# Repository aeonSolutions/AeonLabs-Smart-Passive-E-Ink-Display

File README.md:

[PCB-Prototyping-Catalogue](https://github.com/aeonSolutions/PCB-Prototyping-Catalogue)  >>  [Smart LCD Touch Displays](https://github.com/aeonSolutions/PCB-Prototyping-Catalogue/tree/main/Smart%20LCD%20Touch%20Displays)  >>  Smart Passive 2.13 E-Ink Display

<br>

# Smart Passive 2.13 E-Ink Display

A PCB for a 2.13" E-Ink Display. Requires #no #power an can be configured using @AeonlabsS E-Ink Configuration Device (#EInkCD). Suitable for #commerce or #warehouse shelves for #labelling or #price tagging. Total cost, including the E-Ink Display starts at only 10 euros. Already assembled.

*Don't forget to LIKE , SHARE and subscribe the free whatsApp group* and if you liked this PCB consider buying me a cup of coffee. Links below.
 
### Status
  Waiting to be tested.

If you already tested this PCB send me a message. Thank you

## Versions
### AeonLabs improved Hot Solder Reflow Plate
- revision 2.x (ToDo)
  - Android App to view and control the E-Ink passive Display

- revison 1.x
  - PCB for the 2.9" E-Ink Passive Display. No batteries or power required.

## Liked it ? Get a Free PCB for yourself
Send me your Device or hardware and i will design a custom PCB for it. Free of charge. Contact-me on WhatsApp or email for more info. 

|  | *Don't forget to **LIKE** , **SHARE** and **subscribe** the free chat groups* and if you downloaded one of AeonLabs's PCBs consider sponsor  any open hardware project with a donation or a cup of coffee. Links on the top, right side pane and below. |
|-------------|------|

<br />
<br />

## Q&A WhatsApp/Telegram Groups
|  | Subscribe to the WhatsApp or Telegram channel to get latest information about any of this KiCad projects and get help. Or simply like this kind of projects and want to stay updated with the latest research ideas and prototypes during the day and week.   |
|-------------|------|

<br />
<br />
<br />

## Youtube Channel
|  | Subscribe to my Youtube channel for PCB assembly instruction or any other related to Artificial Intelligence, Smart devices and robotics. Link to the channel [here](https://www.youtube.com/channel/UCAewCBpMRPGCyFc1ET5CHJw). My most recent video is .... |
|-------------|------|

________________________________________________________________________________________________________________
## [Go back to main catalogue page](https://github.com/aeonSolutions/PCB-Prototyping-Catalogue)
________________________________________________________________________________________________________________

#### PCB Parts list:
- 2.9" E-Ink Display: https://s.click.aliexpress.com/e/_DB3wagr
- FPC 24 pin connector: https://s.click.aliexpress.com/e/_AEUWtr
- FPC 10 pint connector: https://s.click.aliexpress.com/e/_AEUWtr
- SMD capacitors: https://s.click.aliexpress.com/e/_Asa5qd

## Fully assembled PCB
|  | To all those not into electronics and still liked and want to own any of the listed PCB for smart devices can buy one on Tindie. |
|-------------|------|

The price starts at 30eur plus postage fees.
(I will also deliver the assembled PCB with all the components in place at a fair aditonal cost).

**Be supportive of my dedication and work towards technology education and buy me a cup of coffee. Link below.**

<br />
<br />
<br />

## Firmware Download / Burner
To make any of the available PCBs here running as intented is needed to download into it a binary program. Anyone can use the PCB available on this repository [AeonLabs-MCU-Burner-USB-to-UART-TTL](https://github.com/aeonSolutions/AeonLabs-MCU-Burner-USB-to-UART-TTL) to fabricate a USB to UART MCU program downloader. Compatible with Arduino Studio, VS Code and Visual Studio programming IDEs (among many others)

<br />
<br />
<br />

______________________________________________________________________________________________________________________________
## Need a custom PCB for your DIY or Maker projects ?
Get a Free PCB for yourself!
Send me your device, hardware or equipment and i will design a custom PCB for it. Free of charge. What i accept:

- Home appliances
- Office appliances
- Industrial and commercial tools, equipment, machinery and appliances.

I will design your custom PCB for your DIY or Maker projects. Free of charge. Contact-me on WhatsApp, Telegram or WeChat to know how. Or email me at mtpsilva@gmail.com for more info.  Links above.

<br />
<br />

______________________________________________________________________________________________________________________________

### PCB Conceptualization and Design
<p align="center">

</p>

<br />
<br />

### PCB Fabrication
<p align="center">

</p>

<br />
<br />

## Author

You can get in touch with me on my LinkedIn Profile:

#### Miguel Tomas

You can also follow my GitHub Profile to stay updated about my latest projects: 

<br>

### Be supportive of my dedication and work towards technology education and buy me a cup of coffee
The PCB Desgin Files i provide here for anyone to use are free. If you like this Smart Device or use it, please consider buying me a cup of coffee, a slice of pizza or a book to help me study, eat and think new PCB design files.

<p align+"left">

<br>

</p>

<br />

### Make a donation on Paypal
Make a donation on paypal and get a TAX refund*.

<br>

### Support all these open hardware projects and become a patreon  
Liked any of my PCB KiCad Designs? Help and Support my open work to all by becomming a LDAD Patreon.
In return I will give a free PCB design in KiCad to all patreon supporters. To learn more go to patreon.com. Link below.

<br />
<br />

______________________________________________________________________________________________________________________________
### License

Before proceeding to download any of AeonLabs software solutions for open-source development and/or PCB hardware electronics development make sure you are choosing the right license for your project. See [AeonLabs Solutions for Open Hardware & Source Development](https://github.com/aeonSolutions/PCB-Prototyping-Catalogue/wiki/AeonLabs-Solutions-for-Open-Hardware-&-Source-Development) for more information. 

______________________________________________________________________________________________________________________________

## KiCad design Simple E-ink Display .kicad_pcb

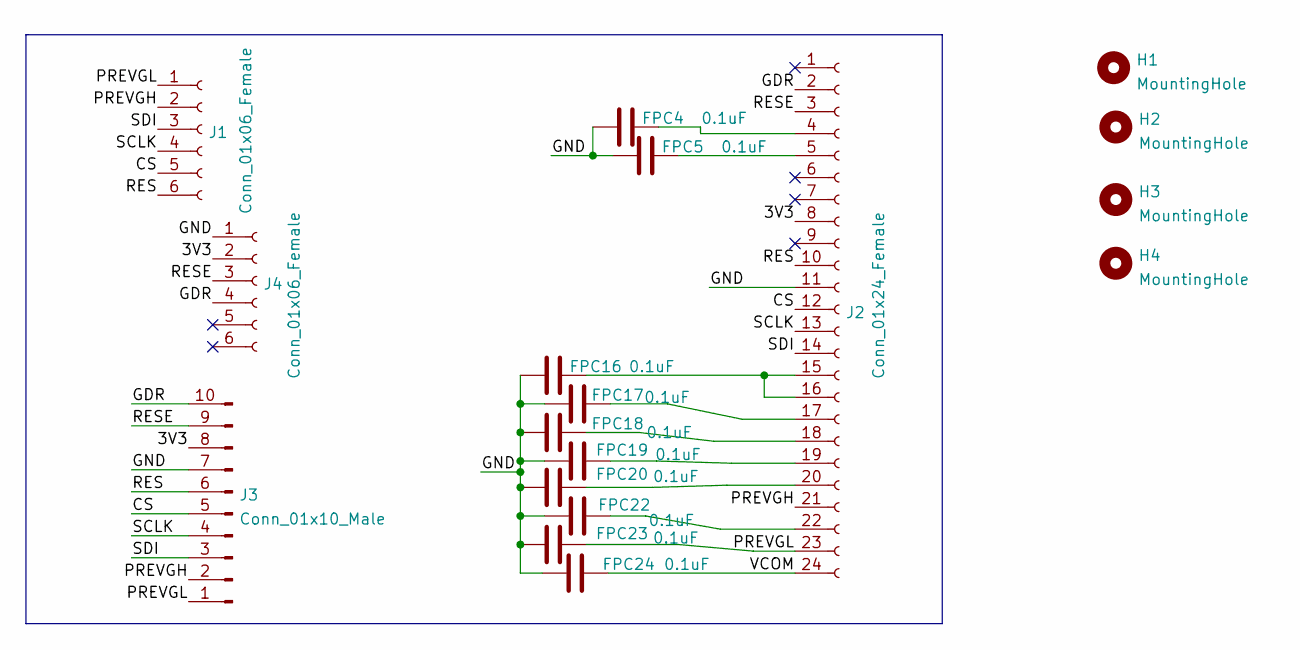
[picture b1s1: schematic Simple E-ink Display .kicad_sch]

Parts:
FPC4, FPC5, FPC16, FPC17, FPC18, FPC19, FPC20, FPC22, FPC23, FPC24: 0.1uF; C_1206_3216MetricTrue
H1, H2, H3, H4: MountingHole; MountingHole_2.1mm
J1, J4: Conn_01x06_Female; pogo 6pin magnetic
J2: Conn_01x24_Female; Hirose_FH12-24S-0.5SH_1x24-1MP_P0.50mm_Horizontal
J3: Conn_01x10_Male; Hirose_FH12-10S-0.5SH_1x10-1MP_P0.50mm_Horizontal

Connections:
/3V3: J2.8, J3.8, J4.2
/CS: J1.5, J2.12, J3.5
/GDR: J2.2, J3.10, J4.4
/GND: FPC4.2, FPC5.2, FPC16.2, FPC17.2, FPC18.2, FPC19.2, FPC20.2, FPC22.2, FPC23.2, FPC24.2, J2.11, J3.7, J4.1
/PREVGH: J1.2, J2.21, J3.2
/PREVGL: FPC23.1, J1.1, J2.23, J3.1
/RES: J1.6, J2.10, J3.6
/RESE: J2.3, J3.9, J4.3
/SCLK: J1.4, J2.13, J3.4
/SDI: J1.3, J2.14, J3.3
/VCOM: FPC24.1, J2.24
unnamed: FPC4.1, J2.4
unnamed: FPC5.1, J2.5
unnamed: FPC16.1, J2.15, J2.16
unnamed: FPC17.1, J2.17
unnamed: FPC18.1, J2.18
unnamed: FPC19.1, J2.19
unnamed: FPC20.1, J2.20
unnamed: FPC22.1, J2.22

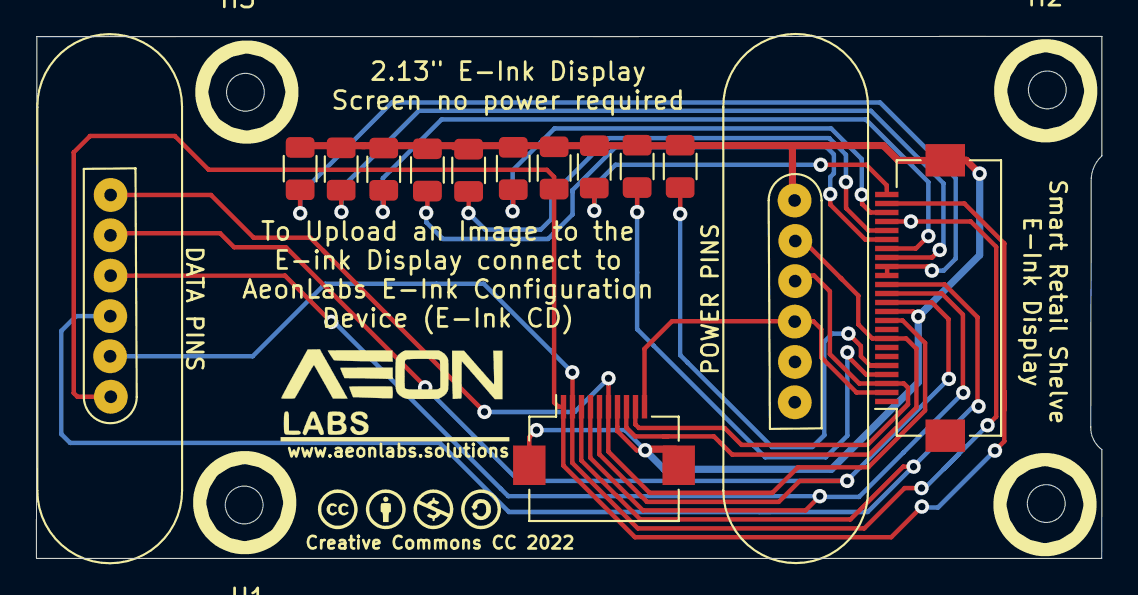
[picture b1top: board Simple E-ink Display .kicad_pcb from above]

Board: 2 copper layers, 59.2 x 29.0 mm, 18 parts (0 on the bottom side), 19 nets.

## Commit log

2022-05-04 revision 1.0
2022-05-04 rev 1.0
2022-05-12 rev 2.1
2022-05-12 new file

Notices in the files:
Simple E-ink Display .kicad_pcb:
License Creative Commons CC 2022
